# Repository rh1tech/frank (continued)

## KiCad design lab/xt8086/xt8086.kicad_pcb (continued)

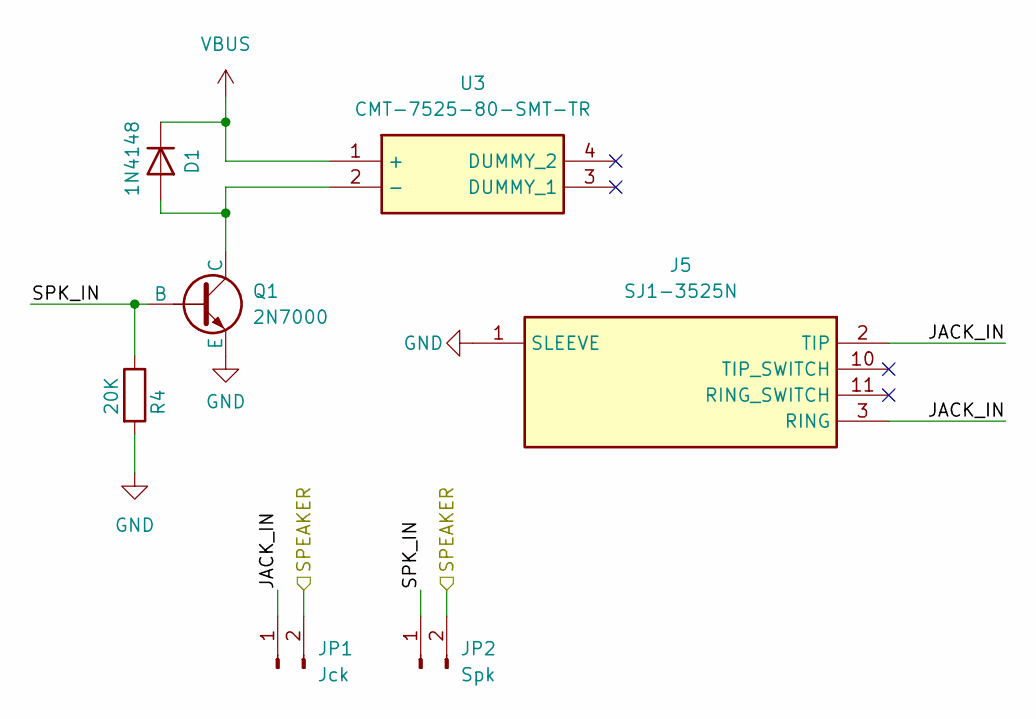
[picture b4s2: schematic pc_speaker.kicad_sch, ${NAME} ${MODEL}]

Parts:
D1: 1N4148; D_SOD-323
J5: SJ1-3525N; AudioJack_3.5mm_SJ1-3525N; Mouser Part Number 490-SJ1-3525N
JP1: Jck; PinHeader_1x02_P2.54mm
JP2: Spk; PinHeader_1x02_P2.54mm
Q1: 2N7000; SOT-23
R4: 20K; R_0805_2012Metric
U3: CMT-7525-80-SMT-TR; Buzzer_SMD_7.5x7.5mm; Mouser Part Number 490-CMT-7525-80SMTTR

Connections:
/Audio/JACK_IN: J5.2 (TIP), J5.3 (RING), JP1.1
/Audio/SPEAKER: JP1.2, JP2.2; also elsewhere on the board
/Audio/SPK_IN: JP2.1, Q1.2 (B), R4.1
GND: J5.1 (SLEEVE), Q1.3 (E), R4.2; also elsewhere on the board
unnamed: D1.2 (A), Q1.1 (C), U3.2 (-)
VBUS: D1.1 (K), U3.1 (+); also elsewhere on the board

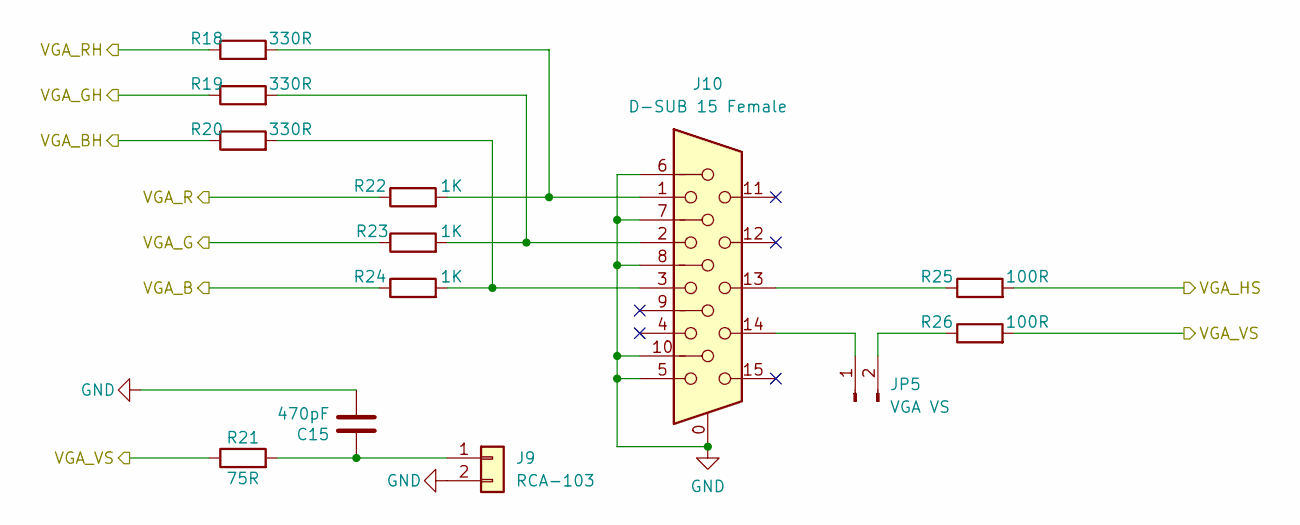
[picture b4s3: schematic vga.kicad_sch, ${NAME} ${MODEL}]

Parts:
C15: 470pF; C_0805_2012Metric
J9: RCA-103; BarrelJack_RCJ-012
J10: D-SUB 15 Female; DSUB-15_Female
JP5: VGA VS; PinHeader_1x02_P2.54mm
R18, R19, R20: 330R; R_0805_2012Metric
R21: 75R; R_0805_2012Metric
R22, R23, R24: 1K; R_0805_2012Metric
R25, R26: 100R; R_0805_2012Metric

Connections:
/PGA2350/GP30: R24.1; also elsewhere on the board
/PGA2350/GP31: R20.1; also elsewhere on the board
/PGA2350/GP32: R23.1; also elsewhere on the board
/PGA2350/GP33: R19.1; also elsewhere on the board
/PGA2350/GP34: R22.1; also elsewhere on the board
/PGA2350/GP35: R18.1; also elsewhere on the board
/PGA2350/GP36: R25.2; also elsewhere on the board
/PGA2350/GP37: R21.1, R26.2; also elsewhere on the board
GND: C15.2, J9.2, J10.0, J10.5, J10.6, J10.7, J10.8, J10.10; also elsewhere on the board
unnamed: C15.1, J9.1, R21.2
unnamed: J10.1, R18.2, R22.2
unnamed: J10.2, R19.2, R23.2
unnamed: J10.3, R20.2, R24.2
unnamed: J10.13, R25.1
unnamed: J10.14, JP5.1
unnamed: JP5.2, R26.1

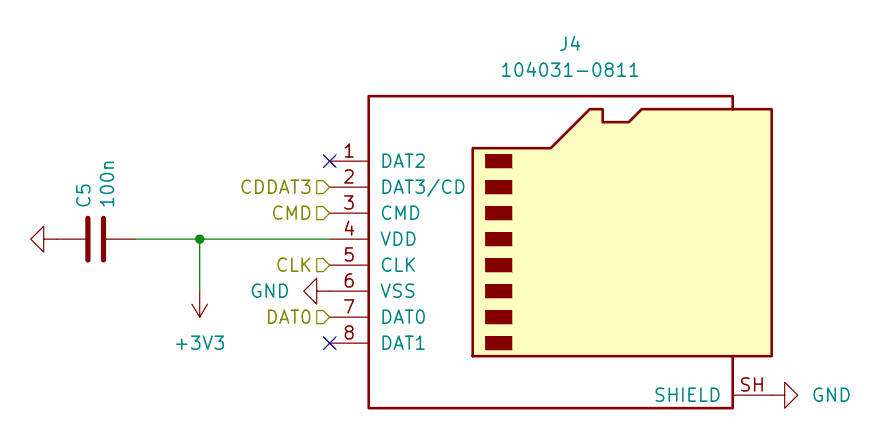
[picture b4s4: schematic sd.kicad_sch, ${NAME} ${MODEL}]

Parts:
C5: 100n; C_0805_2012Metric
J4: 104031-0811; MicroSD_SMD_Long

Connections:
+3V3: C5.2, J4.4 (VDD); also elsewhere on the board
/Micro SD/CDDAT3: J4.2 (DAT3/CD); also elsewhere on the board
/Micro SD/CLK: J4.5 (CLK); also elsewhere on the board
/Micro SD/CMD: J4.3 (CMD); also elsewhere on the board
/Micro SD/DAT0: J4.7 (DAT0); also elsewhere on the board
GND: C5.1, J4.6 (VSS), J4.SH (SHIELD); also elsewhere on the board

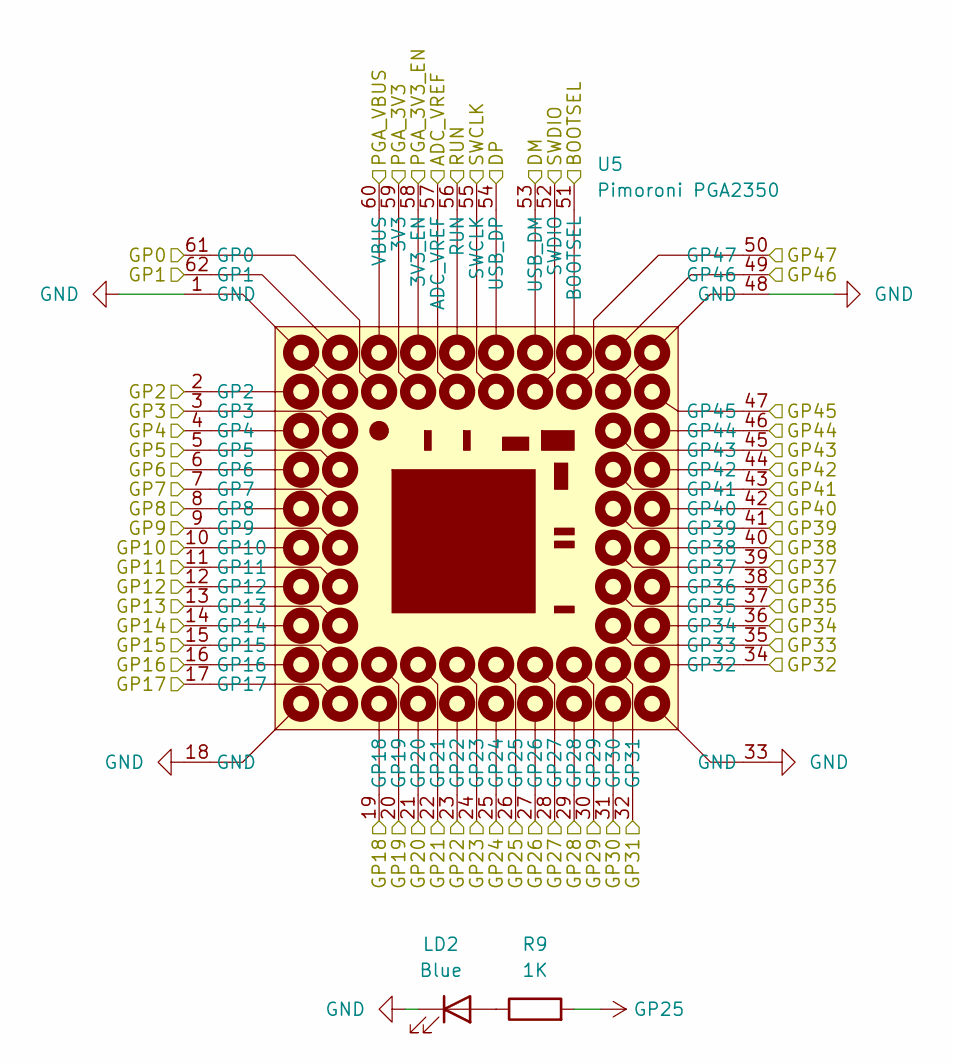
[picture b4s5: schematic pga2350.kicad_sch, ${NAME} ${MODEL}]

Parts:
LD2: Blue; LED_0805_2012Metric_Pad1.15x1.40mm_HandSolder
R9: 1K; R_0805_2012Metric
U5: Pimoroni PGA2350; PGA2350

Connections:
+3V3: U5.59 (3V3); also elsewhere on the board
/A16/GP16: U5.16 (GP16); also elsewhere on the board
/A17/GP17: U5.17 (GP17); also elsewhere on the board
/A18/GP18: U5.19 (GP18); also elsewhere on the board
/A19/GP19: U5.20 (GP19); also elsewhere on the board
/AD0/GP0: U5.61 (GP0); also elsewhere on the board
/AD1/GP1: U5.62 (GP1); also elsewhere on the board
/AD2/GP2: U5.2 (GP2); also elsewhere on the board
/AD3/GP3: U5.3 (GP3); also elsewhere on the board
/AD4/GP4: U5.4 (GP4); also elsewhere on the board
/AD5/GP5: U5.5 (GP5); also elsewhere on the board
/AD6/GP6: U5.6 (GP6); also elsewhere on the board
/AD7/GP7: U5.7 (GP7); also elsewhere on the board
/AD8/GP8: U5.8 (GP8); also elsewhere on the board
/AD9/GP9: U5.9 (GP9); also elsewhere on the board
/AD10/GP10: U5.10 (GP10); also elsewhere on the board
/AD11/GP11: U5.11 (GP11); also elsewhere on the board
/AD12/GP12: U5.12 (GP12); also elsewhere on the board
/AD13/GP13: U5.13 (GP13); also elsewhere on the board
/AD14/GP14: U5.14 (GP14); also elsewhere on the board
/AD15/GP15: U5.15 (GP15); also elsewhere on the board
/ALE/GP20: U5.21 (GP20); also elsewhere on the board
/Audio/SPEAKER: U5.49 (GP46); also elsewhere on the board
/BOOTSEL: U5.51 (BOOTSEL); also elsewhere on the board
/CLK/GP29: U5.30 (GP29); also elsewhere on the board
/GP27: U5.28 (GP27); also elsewhere on the board
/INTA/GP23: U5.24 (GP23); also elsewhere on the board
/INTR/GP26: U5.27 (GP26); also elsewhere on the board
/MIO/GP24: U5.25 (GP24); also elsewhere on the board
/Micro SD/CDDAT3: U5.43 (GP41); also elsewhere on the board
/Micro SD/CLK: U5.44 (GP42); also elsewhere on the board
/Micro SD/CMD: U5.45 (GP43); also elsewhere on the board
/Micro SD/DAT0: U5.42 (GP40); also elsewhere on the board
/PGA2350/ADC_VREF: U5.57 (ADC_VREF)
/PGA2350/DM: U5.53 (USB_DM); also elsewhere on the board
/PGA2350/DP: U5.54 (USB_DP); also elsewhere on the board
/PGA2350/GP30: U5.31 (GP30); also elsewhere on the board
/PGA2350/GP31: U5.32 (GP31); also elsewhere on the board
/PGA2350/GP32: U5.34 (GP32); also elsewhere on the board
/PGA2350/GP33: U5.35 (GP33); also elsewhere on the board
/PGA2350/GP34: U5.36 (GP34); also elsewhere on the board
/PGA2350/GP35: U5.37 (GP35); also elsewhere on the board
/PGA2350/GP36: U5.38 (GP36); also elsewhere on the board
/PGA2350/GP37: U5.39 (GP37); also elsewhere on the board
/PGA2350/GP38: U5.40 (GP38)
/PGA2350/GP39: U5.41 (GP39)
/PGA2350/GP47: U5.50 (GP47)
/PGA2350/PGA_3V3_EN: U5.58 (3V3_EN)
/RD/GP21: U5.22 (GP21); also elsewhere on the board
/RESET/GP28: U5.29 (GP28); also elsewhere on the board
/RUN: U5.56 (RUN); also elsewhere on the board
/SWCLK: U5.55 (SWCLK); also elsewhere on the board
/SWDIO: U5.52 (SWDIO); also elsewhere on the board
/UART0_RX: U5.47 (GP45); also elsewhere on the board
/UART0_TX: U5.46 (GP44); also elsewhere on the board
/WR/GP22: U5.23 (GP22); also elsewhere on the board
GND: LD2.1 (K), U5.1 (GND), U5.18 (GND), U5.33 (GND), U5.48 (GND); also elsewhere on the board
GP25: R9.2, U5.26 (GP25); also elsewhere on the board
unnamed: LD2.2 (A), R9.1
VBUS: U5.60 (VBUS); also elsewhere on the board

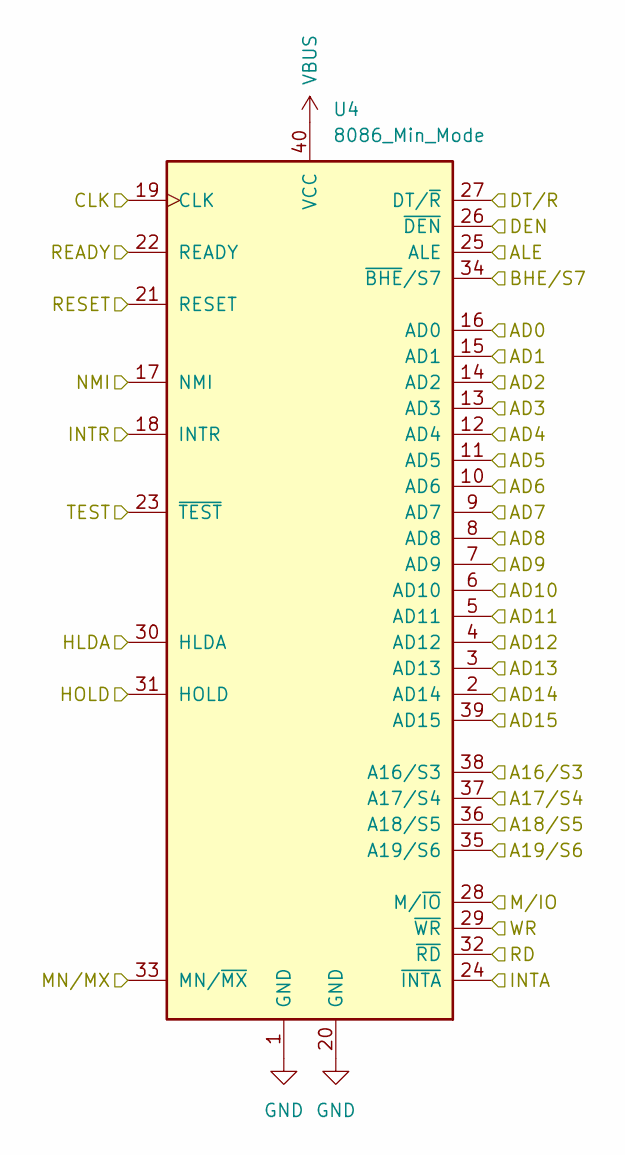
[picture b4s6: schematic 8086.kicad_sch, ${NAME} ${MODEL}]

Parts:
U4: 8086_Min_Mode; DIP-40_W15.24mm

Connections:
/8086/DEN: U4.26 (~DEN)
/8086/DT/R: U4.27 (DT/~R)
/8086/HLDA: U4.30 (HLDA)
/8086/MN/MX: U4.33 (MN/~MX); also elsewhere on the board
/8086/TEST: U4.23 (~TEST); also elsewhere on the board
/A16/GP16: U4.38 (A16/S3); also elsewhere on the board
/A17/GP17: U4.37 (A17/S4); also elsewhere on the board
/A18/GP18: U4.36 (A18/S5); also elsewhere on the board
/A19/GP19: U4.35 (A19/S6); also elsewhere on the board
/AD0/GP0: U4.16 (AD0); also elsewhere on the board
/AD1/GP1: U4.15 (AD1); also elsewhere on the board
/AD2/GP2: U4.14 (AD2); also elsewhere on the board
/AD3/GP3: U4.13 (AD3); also elsewhere on the board
/AD4/GP4: U4.12 (AD4); also elsewhere on the board
/AD5/GP5: U4.11 (AD5); also elsewhere on the board
/AD6/GP6: U4.10 (AD6); also elsewhere on the board
/AD7/GP7: U4.9 (AD7); also elsewhere on the board
/AD8/GP8: U4.8 (AD8); also elsewhere on the board
/AD9/GP9: U4.7 (AD9); also elsewhere on the board
/AD10/GP10: U4.6 (AD10); also elsewhere on the board
/AD11/GP11: U4.5 (AD11); also elsewhere on the board
/AD12/GP12: U4.4 (AD12); also elsewhere on the board
/AD13/GP13: U4.3 (AD13); also elsewhere on the board
/AD14/GP14: U4.2 (AD14); also elsewhere on the board
/AD15/GP15: U4.39 (AD15); also elsewhere on the board
/ALE/GP20: U4.25 (ALE); also elsewhere on the board
/CLK/GP29: U4.19 (CLK); also elsewhere on the board
/INTA/GP23: U4.24 (~INTA); also elsewhere on the board
/INTR/GP26: U4.18 (INTR); also elsewhere on the board
/MIO/GP24: U4.28 (M/~IO); also elsewhere on the board
/RD/GP21: U4.32 (~RD); also elsewhere on the board
/READY: U4.22 (READY); also elsewhere on the board
/RESET/GP28: U4.21 (RESET); also elsewhere on the board
/WR/GP22: U4.29 (~WR); also elsewhere on the board
GND: U4.1 (GND), U4.17 (NMI), U4.20 (GND), U4.31 (HOLD); also elsewhere on the board
GP25: U4.34 (~BHE/S7); also elsewhere on the board
VBUS: U4.40 (VCC); also elsewhere on the board

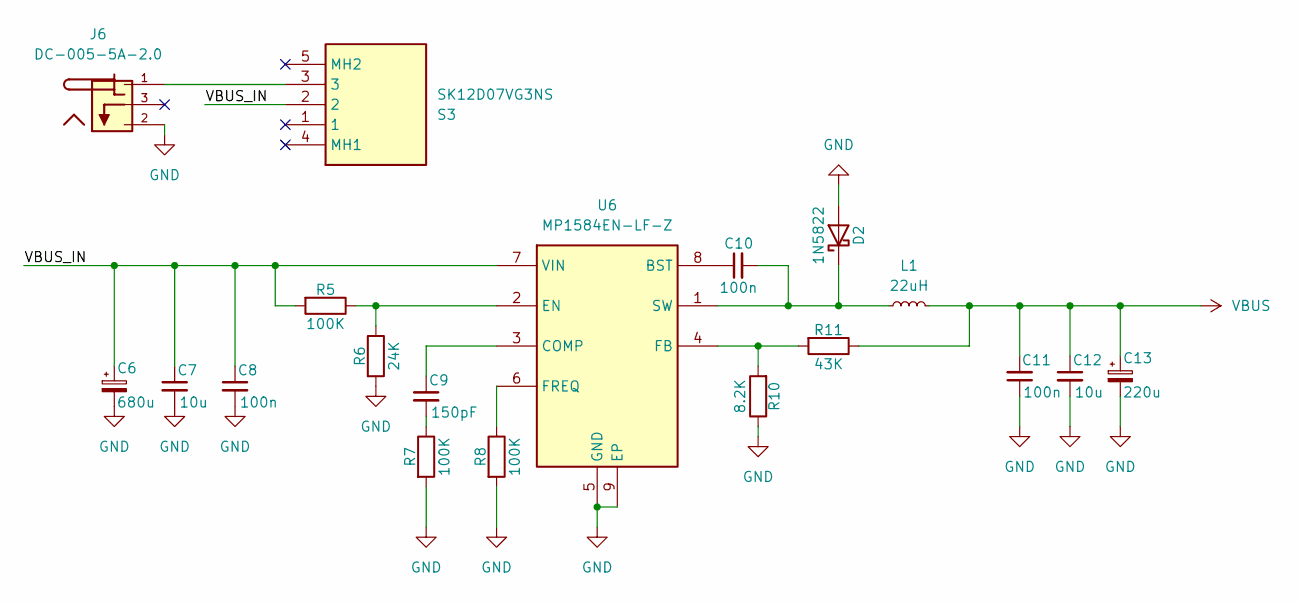
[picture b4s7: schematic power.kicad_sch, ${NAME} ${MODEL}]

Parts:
C6: 680u; C_Radial_D8.0mm_P3.50mm
C7, C12: 10u; C_0805_2012Metric
C8, C10, C11: 100n; C_0805_2012Metric
C9: 150pF; R_0805_2012Metric
C13: 220u; C_Radial_D6.3mm_P2.50mm
D2: 1N5822; D_SMA_SS34
J6: DC-005-5A-2.0; BarrelJack_DC-005; PARTREV A0
L1: 22uH; L_Radial_D9.5mm_P5.00mm_Fastron_07HVP
R5, R7, R8: 100K; R_0805_2012Metric
R6: 24K; R_0805_2012Metric
R10: 8.2K; R_0805_2012Metric
R11: 43K; R_0805_2012Metric
S3: SK12D07VG3NS; Switch_Slide_SK12D07VG3NS; Mouser Part Number 611-SK12D07VG3NS
U6: MP1584EN-LF-Z; SOIC-9_P1.27mm; Mouser Part Number 946-MP1584ENLFZ

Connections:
/Power/VBUS_IN: C6.1, C7.1, C8.1, R5.2, S3.2, U6.7 (VIN)
GND: C6.2, C7.2, C8.2, C11.1, C12.2, C13.2, D2.2 (A), J6.2, R6.2, R7.2, R8.2, R10.1, U6.5 (GND), U6.9 (EP); also elsewhere on the board
unnamed: C9.2, R7.1
unnamed: C10.2, D2.1 (K), L1.1, U6.1 (SW)
unnamed: J6.1, S3.3
unnamed: C10.1, U6.8 (BST)
unnamed: C9.1, U6.3 (COMP)
unnamed: R5.1, R6.1, U6.2 (EN)
unnamed: R10.2, R11.2, U6.4 (FB)
unnamed: R8.1, U6.6 (FREQ)
VBUS: C11.2, C12.1, C13.1, L1.2, R11.1; also elsewhere on the board

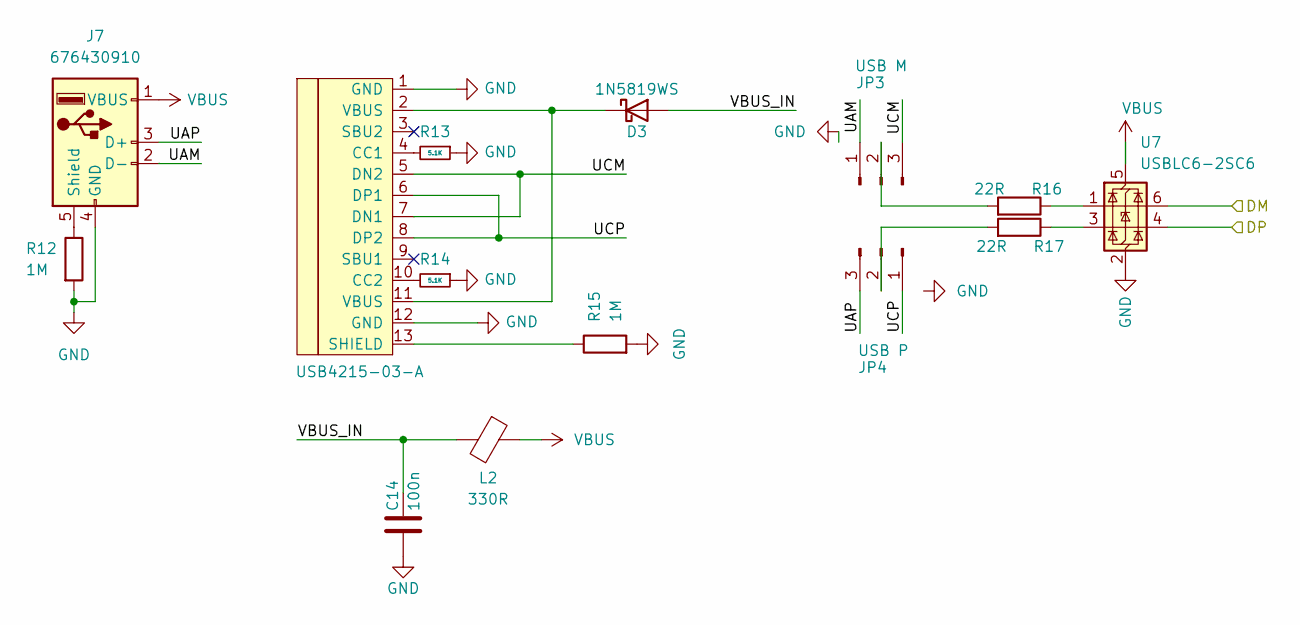
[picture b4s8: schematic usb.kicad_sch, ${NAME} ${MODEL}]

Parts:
C14: 100n; C_0805_2012Metric
D3: 1N5819WS; D_SOD-323
J7: 676430910; USB_A_Single
J8: USB4215-03-A; USB_C_Receptacle; LCSC C165948
JP3: USB M; PinHeader_1x03_P2.54mm_Vertical
JP4: USB P; PinHeader_1x03_P2.54mm_Vertical
L2: 330R; R_0805_2012Metric
R12, R15: 1M; R_0805_2012Metric
R13, R14: 5.1K; R_0805_2012Metric
R16, R17: 22R; R_0805_2012Metric
U7: USBLC6-2SC6; SOT-23-6

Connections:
/PGA2350/DM: U7.6 (I/O1); also elsewhere on the board
/PGA2350/DP: U7.4 (I/O2); also elsewhere on the board
/USB/UAM: J7.2 (D-), JP3.1
/USB/UAP: J7.3 (D+), JP4.3
/USB/UCM: J8.5 (DN2), J8.7 (DN1), JP3.3
/USB/UCP: J8.6 (DP1), J8.8 (DP2), JP4.1
/USB/VBUS_IN: C14.1, D3.2 (A), L2.2
GND: C14.2, J7.4 (GND), J8.1 (GND), J8.12 (GND), R12.2, R13.1, R14.1, R15.2, U7.2 (GND); also elsewhere on the board
unnamed: D3.1 (K), J8.2 (VBUS), J8.11 (VBUS)
unnamed: J7.5 (Shield), R12.1
unnamed: J8.4 (CC1), R13.2
unnamed: J8.10 (CC2), R14.2
unnamed: J8.13 (SHIELD), R15.1
unnamed: JP3.2, R16.2
unnamed: JP4.2, R17.2
unnamed: R16.1, U7.1 (I/O1)
unnamed: R17.1, U7.3 (I/O2)
VBUS: J7.1 (VBUS), L2.1, U7.5 (VBUS); also elsewhere on the board

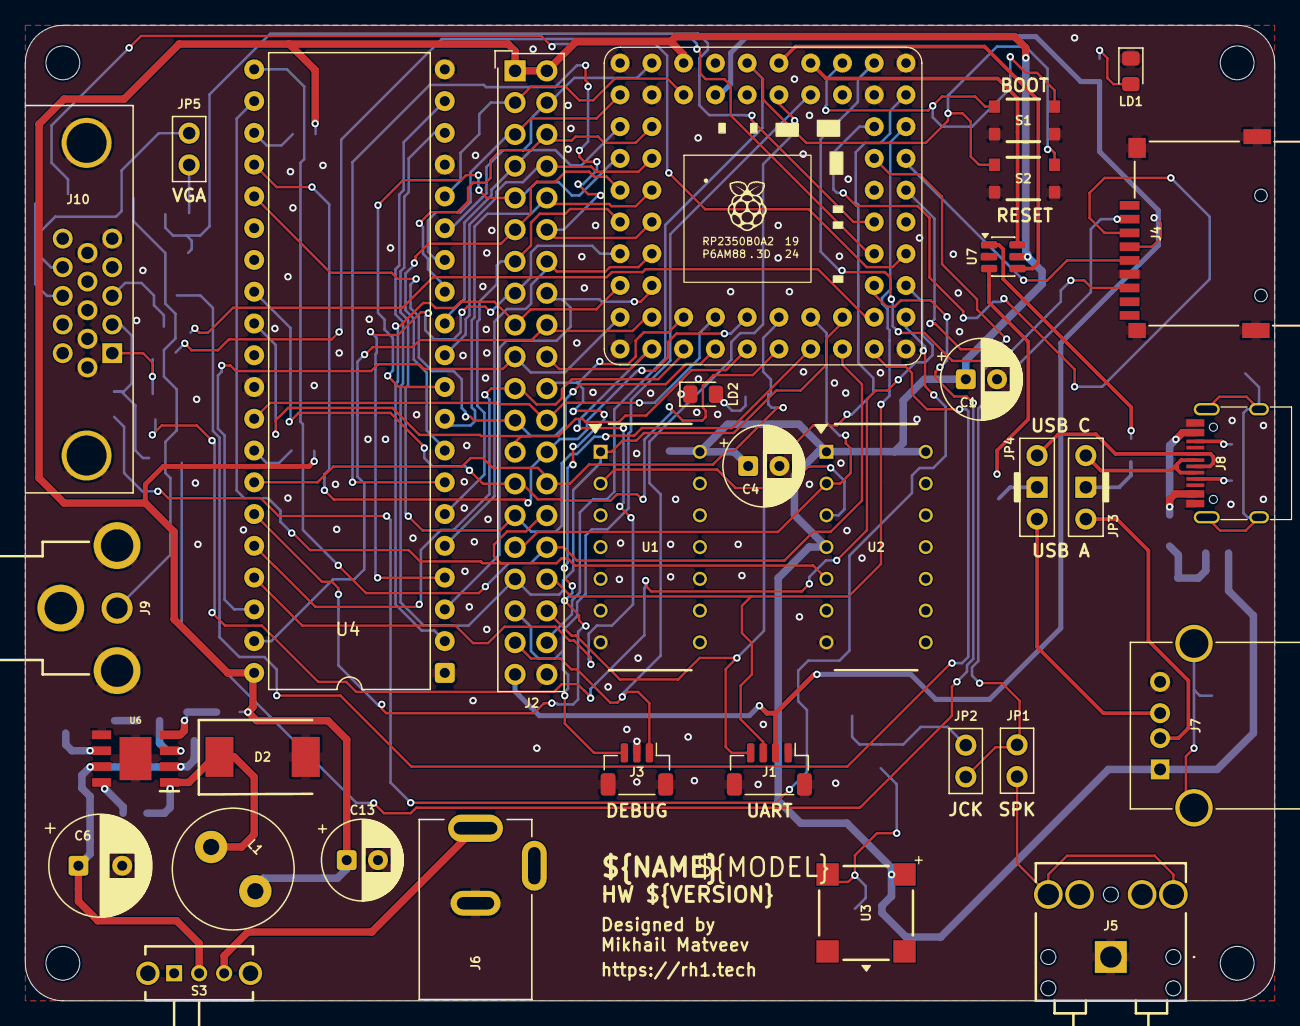
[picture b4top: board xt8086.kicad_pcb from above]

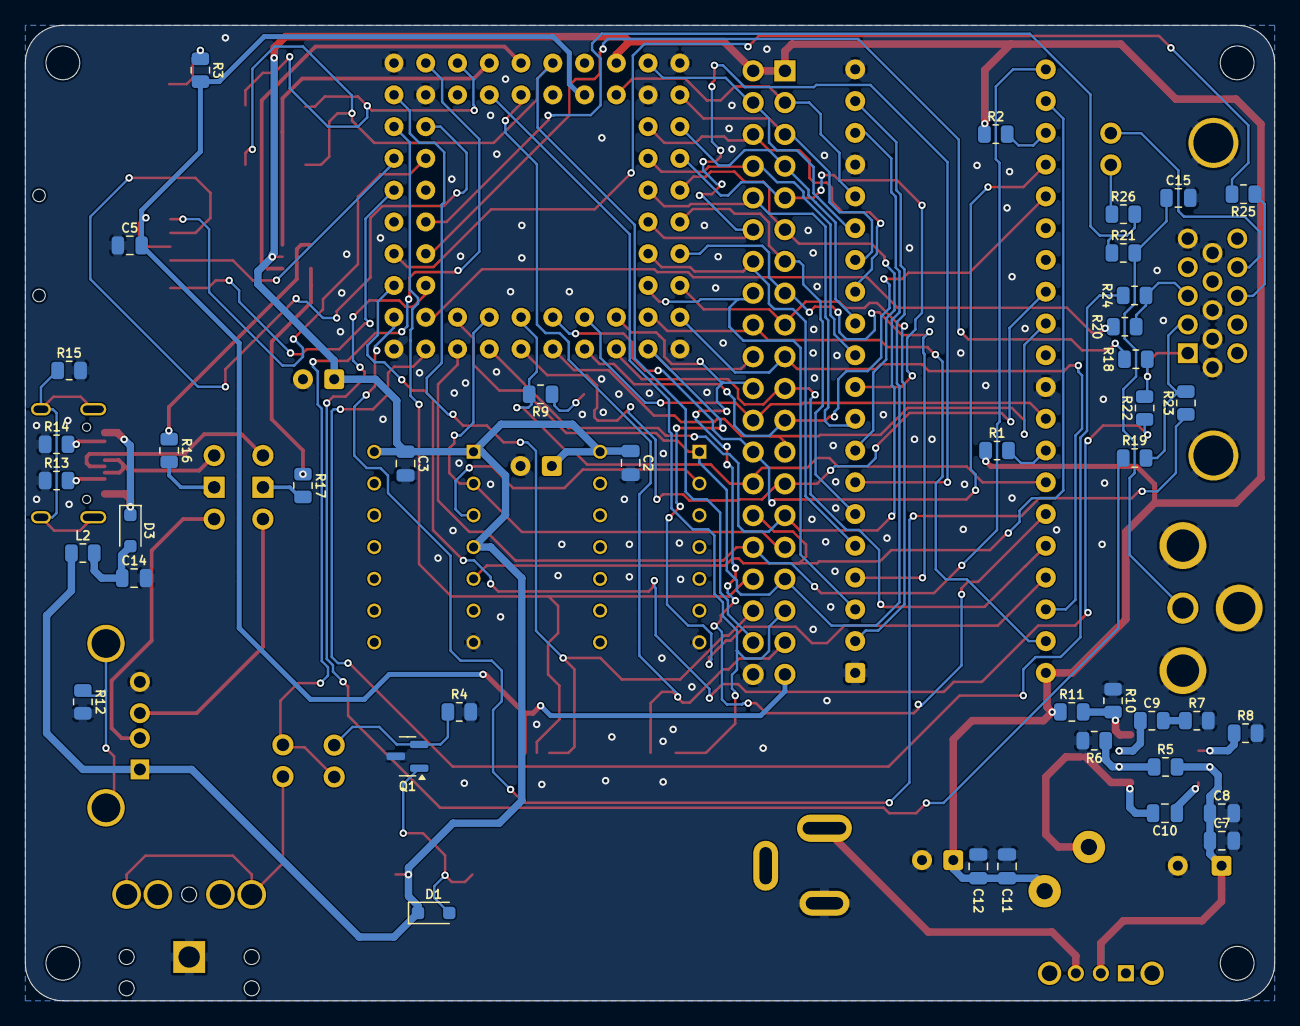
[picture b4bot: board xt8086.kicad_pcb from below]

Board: 2 copper layers, 99.9 x 78.0 mm, 78 parts (41 on the bottom side), 93 nets.

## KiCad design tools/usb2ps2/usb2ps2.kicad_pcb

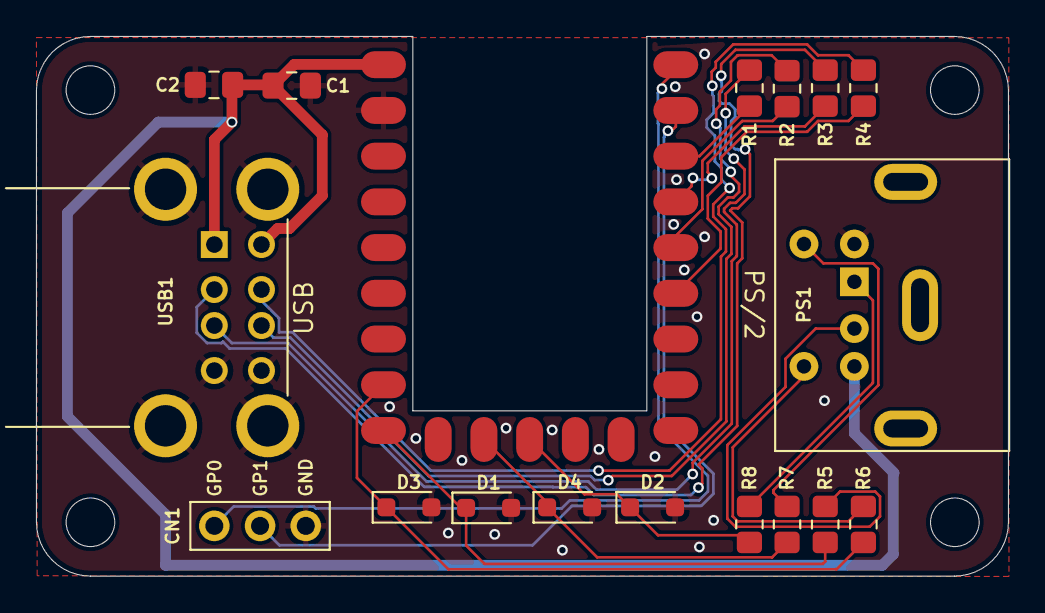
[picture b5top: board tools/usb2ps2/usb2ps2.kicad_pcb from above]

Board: 2 copper layers, 54.0 x 30.0 mm, 22 parts (0 on the bottom side), 20 nets.

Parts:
C1, C2: 10u; Capacitor (0805)
CN1: UART; Pin Header (1x03)
D1, D2, D3, D4: 3V3; Diode (SOD-323)
H1, H2, H3, H4: MountingHole; Mounting Hole (2.7mm)
PS1: PS/2; MiniDIN (6 Pin, female)
R1, R2, R3, R4: 22R; Resistor (0805)
R5, R6, R7, R8: 100R; Resistor (0805)
RP1: RP 2040 Zero; Raspberry Pi Zero (on board)
USB1: USB_A_Stacked; USB Type A (stacked)

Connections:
/GPIO0: CN1.1, RP1.1 (0)
/GPIO1: CN1.2, RP1.2 (1)
/GPIO2: R1.1, RP1.3 (2)
/GPIO3: R3.1, RP1.4 (3)
/GPIO4: R2.1, RP1.5 (4)
/GPIO5: R4.1, RP1.6 (5)
/GPIO11: D2.1 (K), R8.2, RP1.12 (11)
/GPIO12: D4.1 (K), R7.2, RP1.13 (12)
/GPIO14: D1.1 (K), R5.2, RP1.15 (14)
/GPIO15: D3.1 (K), R6.2, RP1.16 (15)
/PS2 with Diodes/KB_CLK: PS1.5, R7.1
/PS2 with Diodes/KB_DATA: PS1.1, R8.1
/PS2 with Diodes/MS_CLK: PS1.6, R6.1
/PS2 with Diodes/MS_DATA: PS1.2, R5.1
GND: C1.2, C2.2, CN1.3, D1.2 (A), D2.2 (A), D3.2 (A), D4.2 (A), PS1.3, RP1.22 (GND), USB1.4 (GND1), USB1.8 (GND2), USB1.9 (Shield)
unnamed: R1.2, USB1.3 (D1+)
unnamed: R3.2, USB1.2 (D1-)
unnamed: R2.2, USB1.7 (D2+)
unnamed: R4.2, USB1.6 (D2-)
VBUS: C1.1, C2.1, PS1.4, RP1.23 (5V), USB1.1 (VBUS1), USB1.5 (VBUS2)
